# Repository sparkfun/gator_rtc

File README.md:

SparkFun gator:RTC - micro:bit Accessory Board
=============================

[*SparkFun gator:RTC - micro:bit Accessory Board (COM-15486)*](https://www.sparkfun.com/products/15486)  

The gator:RTC is a supplemental data logging tool to be used in conjunction with the [gator:log](https://www.sparkfun.com/products/15270), part of SparkFun's gator:bit series of gator-clippable accessories designed for easy interface with the micro:bit or other microcontrollers. This tool allows a student to focus more on the experiment than watching a thermometer or stopwatch.

Instead of using pin connections or requiring soldering, this product provides connection pads for a more kid freindly experience with alligator clips. The design intention of this product is to be used with the [gato:bit (v2)](https://www.sparkfun.com/products/15162), and the [micro:bit development board](https://www.sparkfun.com/products/14208).

Repository Contents
-------------------

* **/Hardware** - Eagle design files (.brd, .sch)

Documentation
--------------

* **[Hookup Guide](https://learn.sparkfun.com/tutorials/sparkfun-gatorrtc-hookup-guide)** - Basic hookup guide for the gator:RTC.
* **[gator:RTC PXT Package](https://github.com/sparkfun/pxt-gator-rtc)** - PXT- package for the MakeCode gator:RTC extension.

License Information
-------------------

This product is _**open source**_! 

Please review the LICENSE.md file for license information. 

If you have any questions or concerns on licensing, please visit the [SparkFun Forum](https://forum.sparkfun.com/index.php) and post a topic. For more general questions related to our gator boards, please visit this section of the forum: [Gator Products](https://forum.sparkfun.com/viewforum.php?f=162).

Distributed as-is; no warranty is given.

- Your friends at SparkFun.

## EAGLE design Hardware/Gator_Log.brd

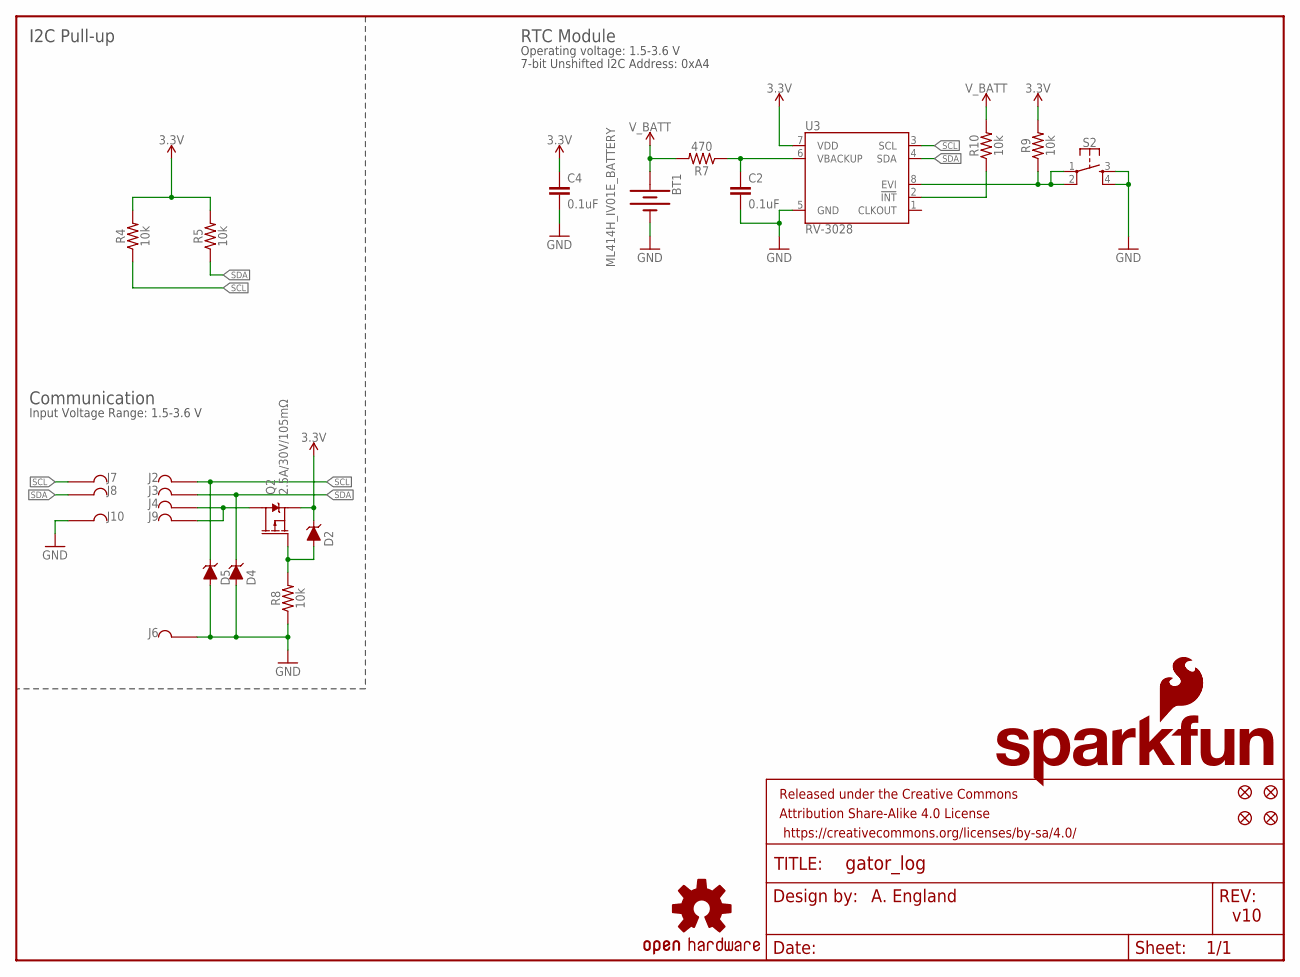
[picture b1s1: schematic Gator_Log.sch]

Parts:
BT1: ML414H_IV01E_BATTERY; ML414H_IV01E
C2, C4: 0.1uF; 0603
D2, D4, D5: 3.6V; SOD-323
FID1, FID2, FID3, FID4: FIDUCIALUFIDUCIAL; FIDUCIAL-MICRO
FRAME1: FRAME-LETTER; CREATIVE_COMMONS
J2, J3, J4, J6, J7, J8, J9, J10: GATORGATOR_MINI; GATOR_MINI
LOGO1: SFE_LOGO_FLAME.1_INCH; SFE_LOGO_FLAME_.1
LOGO2: OSHW-LOGOMINI; OSHW-LOGO-MINI
LOGO4: SFE_LOGO_NAME_FLAME.1_INCH; SFE_LOGO_NAME_FLAME_.1
Q2: 2.5A/30V/105mΩ; SOT23-3
R4, R5, R8, R9, R10: 10k; 0603
R7: 470; 0603
S2: MOMENTARY-SWITCH-SPST-2-SMD-5.2MM-TALL; TACTILE_SWITCH_SMD_5.2MM
U3: RV-3028

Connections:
3.3V: C4.1, D2.C, Q2.2 (S), R4.2, R5.2, R9.2, U3.7 (VDD)
!RST: R10.1, U3.2 (!INT)
GND: BT1.-, C2.2, C4.2, D4.A, D5.A, J6.P$2, J10.P$2, R8.1, S2.3, S2.4, U3.5 (GND)
unnamed: J4.P$2, J9.P$2, Q2.3 (D)
unnamed: D2.A, Q2.1 (G), R8.2
unnamed: R9.1, S2.1, S2.2, U3.8 (EVI)
SCL: D5.C, J2.P$2, J7.P$2, R4.1, U3.3 (SCL)
SDA: D4.C, J3.P$2, J8.P$2, R5.1, U3.4 (SDA)
VBACKUP: C2.1, R7.1, U3.6 (VBACKUP)
V_BATT: BT1.+, R7.2, R10.2

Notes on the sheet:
v10
A. England
I2C Pull-up
Communication
RTC Module
Operating voltage: 1.5-3.6 V
7-bit Unshifted I2C Address: 0xA4
Input Voltage Range: 1.5-3.6 V

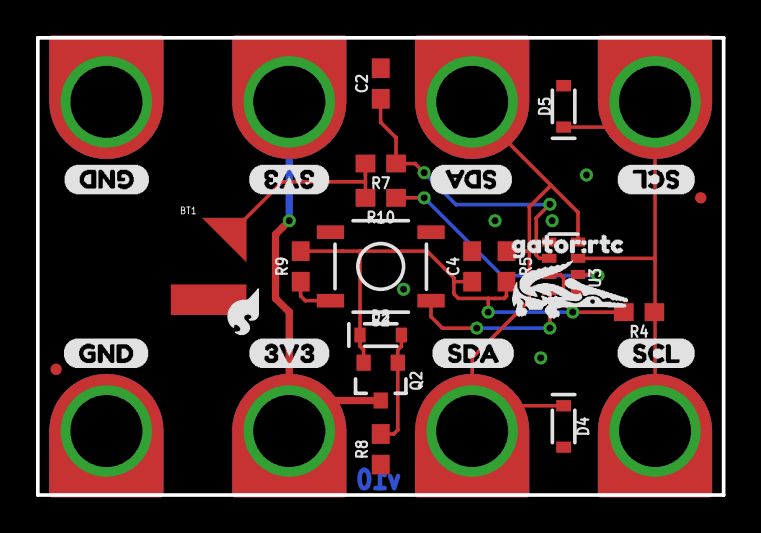
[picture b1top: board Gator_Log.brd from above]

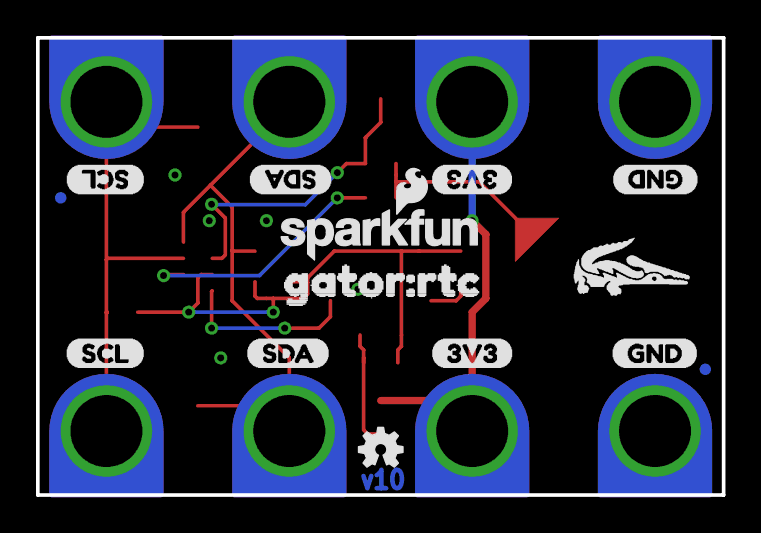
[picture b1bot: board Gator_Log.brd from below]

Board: 2 copper layers, 38.1 x 25.4 mm, 52 parts (14 on the bottom side), 10 nets.

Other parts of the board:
U$1, U$3, U$12, U$15: 3V33
U$2, U$10, U$11, U$23: GND0
U$4, U$7, U$13, U$16: SDA1
U$5, U$6, U$14, U$18: SCL2
U$8, U$21: GATORBIT_FINAL_FOR_SILK#01#PNG
U$20, U$24: GATOR#RTC0
U$22: ORDERING_INSTRUCTIONS

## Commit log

2019-07-17 had wrong files
2019-07-18 post checklist changes
2019-08-02 adding in gitignore
2019-09-04 Update to proper product

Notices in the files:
parts and their libraries:
SparkFun-Connectors: Licensing: Creative Commons ShareAlike 4.0 International - https://creativecommons.org/licenses/by-sa/4.0
SparkFun-Aesthetics: Released under the Creative Commons Attribution Share-Alike 4.0 License
SparkFun-Aesthetics: https://creativecommons.org/licenses/by-sa/4.0
